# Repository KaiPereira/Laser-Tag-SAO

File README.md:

# Laser Tag SAOs

These are little badge add-ons so you can play laser-tag against your friends :D 

- VSLY5940 Narrow beam IR transmitter
- TSOP38438 IR receiver
- NPN for turning on the IR transmitter
- SMD4020 side mount neopixels
- 0.91" 128x32 OLED/display for funsies
- PS1240P02BT Piezo buzzer
- Button to shoot and a button to change modes or other stuff
- 1 SAO port
- ATtiny84 DIP 14

## Firmware

You can program the laser tag guns over SPI broken out over the SAO connector.

First bridge the jumpers on the back with solder.

Next, you'll need to setup your Arduino as an ISP. I've set mine up for use with the Pi Pico, so you'll need to modify the ISP code for other boards. 
- Select your board by going tools -> boards -> whatever board you're using. For the raspberry pi, you'll need to install it in the board manager tab. 
- Upload the ArduinoISP code in [/programming/ArduinoISP](/programming/ArduinoISP).

Then you should open up the PCB in KiCad and wire up the SAO connector to the Pi Pico, I'll make a second version with silkscreen labels in the future:
- 3.3V to 3.3V
- GND to GND
- IO19 to MOSI
- IO18 to SCK
- IO16 to MISO
- GPIO10 to RESET

Then change the board to be the ATtiny24/44/84 No bootloader from the ATTinyCore library and set tools -> programmer to be "Arduino as ISP".

Next run tools -> burn bootloader and then upload the ATtiny code in [/programming/laser-tag](/programming/laser-tag) and you're all flashed!

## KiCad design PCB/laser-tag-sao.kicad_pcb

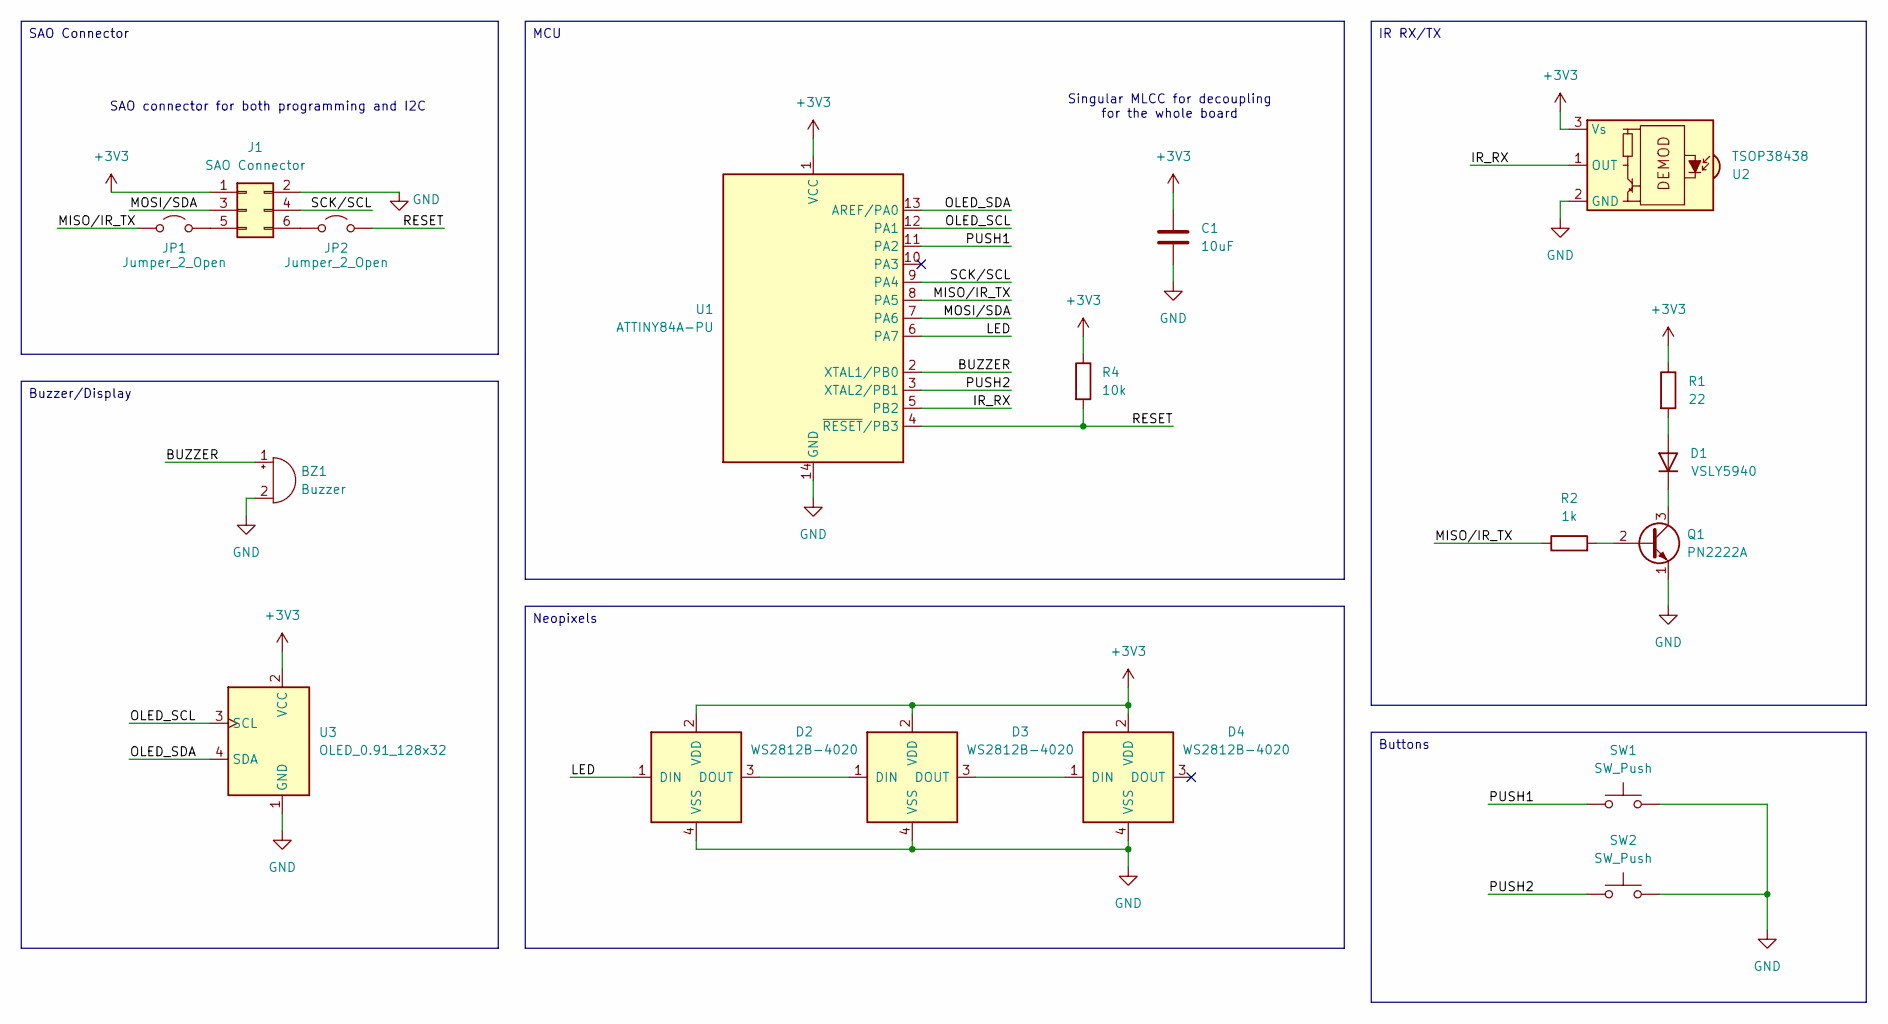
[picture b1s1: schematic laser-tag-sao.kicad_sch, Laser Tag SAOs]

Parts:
BZ1: Buzzer; Buzzer_TDK_PS1240P02BT_D12.2mm_H6.5mm; Digikey Part # 445-2525-1-ND - Cut Tape (CT)
C1: 10uF; C_Disc_D5.0mm_W2.5mm_P2.50mm; Digikey Part # 445-173132-1-ND - Cut Tape (CT)
D1: VSLY5940; LED_D5.0mm; Digikey Part # VSLY5940-ND
D2, D3, D4: WS2812B-4020; LED_WS2812B-4020; PARTREV V1.2
J1: SAO Connector; PinHeader_2x03_P2.54mm_Vertical
JP1, JP2: Jumper_2_Open; SolderJumper-2_P1.3mm_Open_RoundedPad1.0x1.5mm
Q1: PN2222A; TO-92_Inline
R1: 22; R_Axial_DIN0204_L3.6mm_D1.6mm_P5.08mm_Horizontal; Digikey Part # CF18JT22R0TR-ND - Tape & Reel (TR)
R2: 1k; R_Axial_DIN0204_L3.6mm_D1.6mm_P5.08mm_Horizontal; Digikey Part # CF18JT1K00TR-ND - Tape & Reel (TR)
R4: 10k; R_Axial_DIN0204_L3.6mm_D1.6mm_P5.08mm_Horizontal; Digikey Part # CF18JT10K0TR-ND - Tape & Reel (TR)
SW1: SW_Push; SW_PUSH_6mm; Digikey Part # 450-1650-ND
SW2: SW_Push; SW_PUSH_6mm
U1: ATTINY84A-PU; DIP-14_W7.62mm; Digikey Part # ATTINY84A-PU-ND
U2: TSOP38438; Vishay_MINICAST-3Pin; Digikey Part # TSOP38438-ND
U3: OLED_0.91_128x32

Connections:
+3V3: C1.1, D2.2 (VDD), D3.2 (VDD), D4.2 (VDD), J1.1, R1.1, R4.1, U1.1 (VCC), U2.3 (Vs), U3.2 (VCC)
/BUZZER: BZ1.1 (+), U1.2 (XTAL1/PB0)
/IR_RX: U1.5 (PB2), U2.1 (OUT)
/LED: D2.1 (DIN), U1.6 (PA7)
/MISO/IR_TX: JP1.1 (A), R2.1, U1.8 (PA5)
/MOSI/SDA: J1.3, U1.7 (PA6)
/OLED_SCL: U1.12 (PA1), U3.3 (SCL)
/OLED_SDA: U1.13 (AREF/PA0), U3.4 (SDA)
/PUSH1: SW1.1, U1.11 (PA2)
/PUSH2: SW2.1, U1.3 (XTAL2/PB1)
/RESET: JP2.2 (B), R4.2, U1.4 (~RESET/PB3)
/SCK/SCL: J1.4, U1.9 (PA4)
GND: BZ1.2 (-), C1.2, D2.4 (VSS), D3.4 (VSS), D4.4 (VSS), J1.2, Q1.1 (E), SW1.2, SW2.2, U1.14 (GND), U2.2 (GND), U3.1 (GND)
unnamed: D1.2 (A), R1.2
unnamed: D1.1 (K), Q1.3 (C)
unnamed: D2.3 (DOUT), D3.1 (DIN)
unnamed: D3.3 (DOUT), D4.1 (DIN)
unnamed: J1.5, JP1.2 (B)
unnamed: J1.6, JP2.1 (A)
unnamed: Q1.2 (B), R2.2

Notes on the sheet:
SAO connector for both programming and I2C
Singular MLCC for decoupling for the whole board
IR RX/TX
Neopixels
Buzzer/Display
Buttons
SAO Connector
MCU

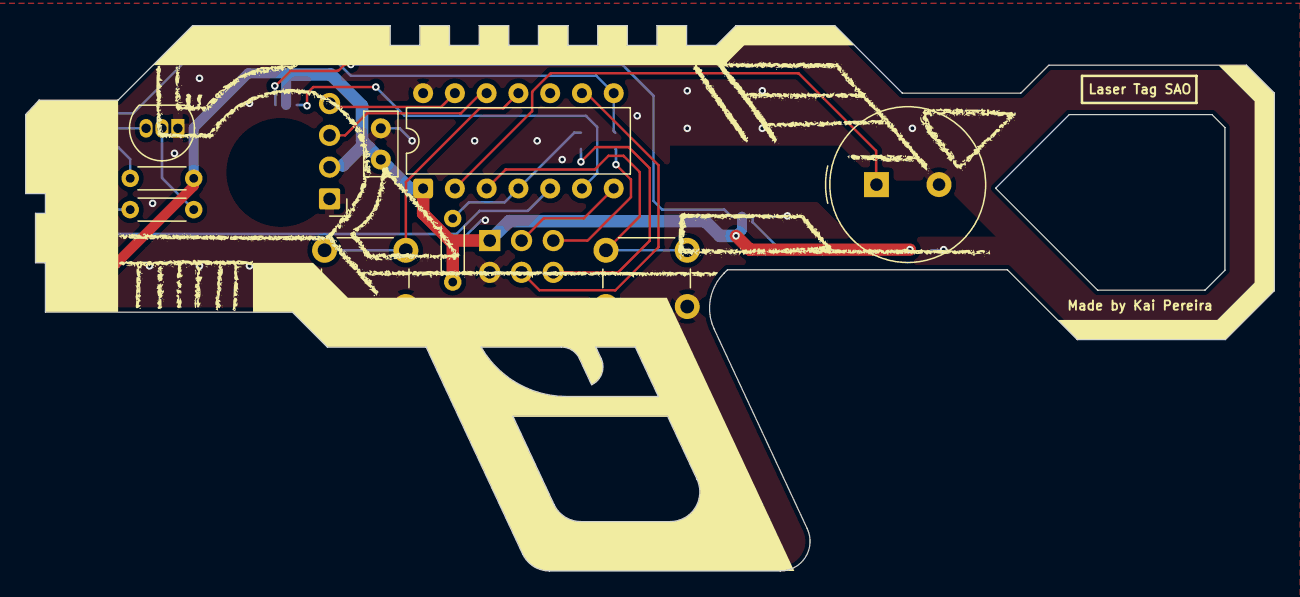
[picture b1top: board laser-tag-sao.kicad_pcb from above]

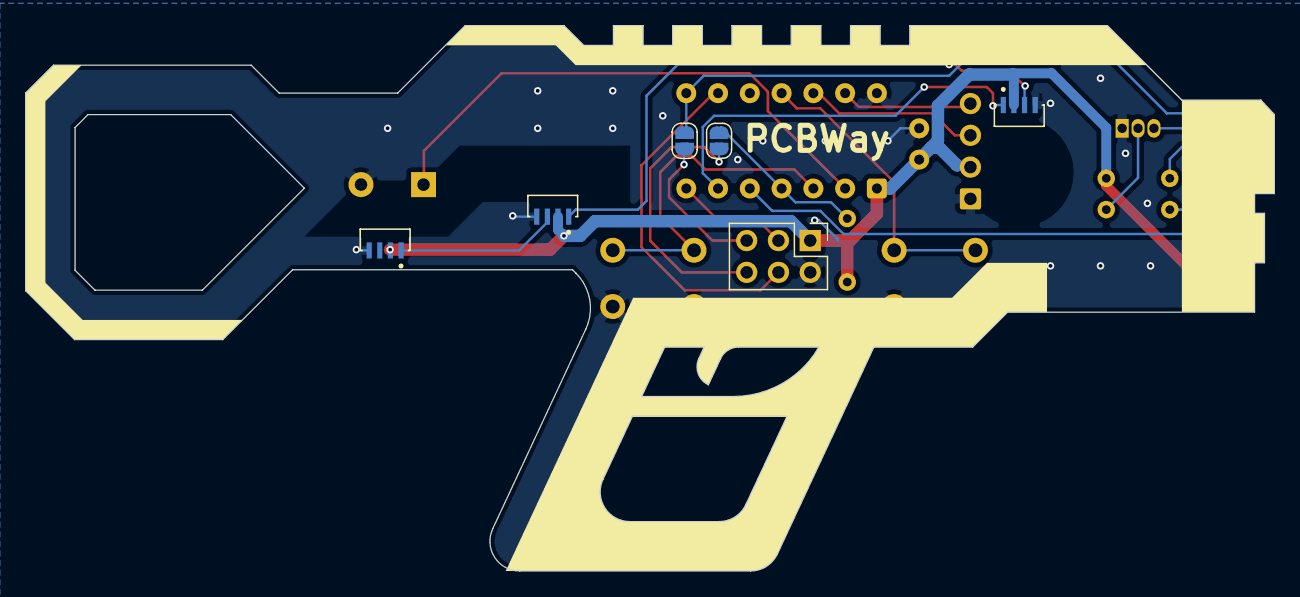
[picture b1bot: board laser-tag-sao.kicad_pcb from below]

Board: 2 copper layers, 99.8 x 43.6 mm, 18 parts (6 on the bottom side), 20 nets.

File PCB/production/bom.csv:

Designator,Footprint,Quantity,Value,LCSC Part #
BZ1,Buzzer_TDK_PS1240P02BT_D12.2mm_H6.5mm,1,Buzzer,
C1,C_Disc_D5.0mm_W2.5mm_P2.50mm,1,10uF,
D1,LED_D5.0mm,1,VSLY5940,
"D2, D3, D4",LED_WS2812B-4020,3,WS2812B-4020,
J1,PinHeader_2x03_P2.54mm_Vertical,1,SAO Connector,
"JP1, JP2",SolderJumper-2_P1.3mm_Open_RoundedPad1.0x1.5mm,2,Jumper_2_Open,
Q1,TO-92_Inline,1,PN2222A,
R1,R_Axial_DIN0204_L3.6mm_D1.6mm_P5.08mm_Horizontal,1,22,
R2,R_Axial_DIN0204_L3.6mm_D1.6mm_P5.08mm_Horizontal,1,1k,
R4,R_Axial_DIN0204_L3.6mm_D1.6mm_P5.08mm_Horizontal,1,10k,
"SW1, SW2",SW_PUSH_6mm,2,SW_Push,
U1,DIP-14_W7.62mm,1,ATTINY84A-PU,
U2,Vishay_MINICAST-3Pin,1,TSOP38438,
U3,OLED_0.91_128x32,1,OLED_0.91_128x32,

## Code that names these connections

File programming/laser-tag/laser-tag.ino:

// Laser tag blaster for ATtiny84 (ATTinyCore)
//
//   Button    PA2 (physical pin 11) -> GND, uses internal pull-up
//   IR TX     PA5 (physical pin 8)  -> NPN base resistor -> VSLY5940
//   Buzzer    PB0 (physical pin 2)
//   IR RX     PB2 (physical pin 5)  <- 38 kHz IR receiver output (TSOP-style, active LOW)
//
// Set Tools > Clock to "8 MHz (internal)" before uploading. setup() also
// clears the clock divider, so Burn Bootloader isn't strictly needed.
//
// IR safety: each shot is ~10 ms of short bursts at <=50% carrier duty,
// with a forced cooldown between shots and the pin always left LOW.

#include <util/delay.h>
#include <avr/power.h>

#ifdef PIN_PA2
  #define BUTTON   PIN_PA2
  #define BUZZER   PIN_PB0
  #define IR_RX    PIN_PB2
#else
  #define BUTTON   2    // ATTinyCore default (counterclockwise) pinmap
  #define BUZZER   10
  #define IR_RX    8
#endif

#define IR_BIT (1 << 5)  // PA5, driven directly on PORTA for accurate timing

// Receiver debug: set to 1 and the buzzer beeps for as long as the IR receiver
// sees any 38 kHz IR (a TV remote, another badge, or this badge's own shot
// bouncing back). Normal hit detection is skipped. Set to 0 for real games.
#define DEBUG_RX 0

// The TSOP38438 receiver is a short-burst (AGC4) type: it treats one long
// continuous 38 kHz burst as noise and suppresses it. So a shot is a train of
// short bursts, like a TV remote, and a hit means seeing enough of them in a row.
const uint8_t  SHOT_PULSES     = 8;     // bursts per shot
const uint8_t  PULSE_CYCLES    = 24;    // ~630 us of 38 kHz per burst
#define        PULSE_GAP_US      630    // IR off between bursts

// Shot power: microseconds the LED is ON in each ~26 us carrier cycle.
// 13 = 50% duty (full power, bounces off walls and hits from anywhere).
// Lower = weaker shot, so only a direct hit counts. The receiver still sees
// the 38 kHz carrier down to ~2. Tune this to taste: try 4, then 2-6.
#define        IR_ON_US          4
const uint8_t  HIT_MIN_PULSES  = 4;     // bursts that must be seen to count as a hit
const uint16_t PULSE_MIN_US    = 200;   // receiver LOW pulse width accepted as a burst
const uint16_t PULSE_MAX_US    = 1500;
const uint16_t GAP_MAX_US      = 1500;  // longer silence ends the shot
const uint16_t COOLDOWN_MS     = 300;   // minimum time between shots (no auto-fire)
const uint16_t HIT_LOCKOUT_MS  = 1000;  // one bolt = one hit
const uint16_t SELF_IGNORE_MS  = 50;    // ignore our own shot's reflections

unsigned long lastShot = 0;
unsigned long lastHit = 0;
bool wasPressed = false;

void irOff() {
  PORTA &= ~IR_BIT;
}

// One shot: SHOT_PULSES short 38 kHz bursts with gaps between them.
// Interrupts are paused so the carrier stays clean.
void fireShot() {
  noInterrupts();
  for (uint8_t p = 0; p < SHOT_PULSES; p++) {
    for (uint8_t i = 0; i < PULSE_CYCLES; i++) {
      PORTA |= IR_BIT;
      _delay_us(IR_ON_US);
      PORTA &= ~IR_BIT;
      _delay_us(25 - IR_ON_US);  // ~1 us of loop overhead at 8 MHz
    }
    _delay_us(PULSE_GAP_US);
  }
  irOff();
  interrupts();
}

// Descending "pew" laser sound, about 130 ms.
void pew() {
  for (int f = 3000; f > 400; f -= 100) {
    tone(BUZZER, f);
    delay(5);
  }
  noTone(BUZZER);
  digitalWrite(BUZZER, LOW);
}

// "You got hit": a crunchy falling zap, then a two-note "you're down" sting.
// About 0.8 s total.
void hitSound() {
  // Falling zap; alternating between f and 3/4 f gives it a gritty, electric edge
  for (int f = 1800; f > 150; f -= 40) {
    tone(BUZZER, ((f / 40) % 2) ? f : f * 3 / 4);
    delay(8);
  }
  noTone(BUZZER);
  delay(60);

  // Two descending notes
  tone(BUZZER, 400);
  delay(120);
  noTone(BUZZER);
  delay(40);
  tone(BUZZER, 250);
  delay(250);

  noTone(BUZZER);
  digitalWrite(BUZZER, LOW);
}

// Returns true if the receiver shows a shot: several short LOW pulses in a row.
// The first pulse can be any length, since we may have started watching midway.
bool checkForBolt() {
  if (digitalRead(IR_RX) == HIGH) return false;  // nothing seen

  uint8_t pulses = 0;
  while (true) {
    // Receiver LOW = burst
    unsigned long start = micros();
    while (digitalRead(IR_RX) == LOW) {
      if (micros() - start > PULSE_MAX_US) {
        // Too long to be one of our bursts: let it clear (bounded) and give up
        unsigned long t = micros();
        while (digitalRead(IR_RX) == LOW && micros() - t < 50000UL) {}
        return false;
      }
    }
    if (pulses > 0 && micros() - start < PULSE_MIN_US) return false;  // glitch
    if (++pulses >= HIT_MIN_PULSES) return true;

    // Receiver HIGH = gap; wait for the next burst
    start = micros();
    while (digitalRead(IR_RX) == HIGH) {
      if (micros() - start > GAP_MAX_US) return false;
    }
  }
}

void setup() {
  // New ATtiny84s ship with the CKDIV8 fuse set (8 MHz / 8 = 1 MHz), which makes
  // every sound 8x slower and deeper and puts the IR carrier at ~5 kHz.
  // Force the full 8 MHz in software so it works even if the fuses were never burned.
  clock_prescale_set(clock_div_1);

  irOff();          // LOW before making it an output, so the LED never blips on
  DDRA |= IR_BIT;
  pinMode(BUZZER, OUTPUT);
  pinMode(BUTTON, INPUT_PULLUP);
  pinMode(IR_RX, INPUT_PULLUP);  // most receivers have one built in; this doesn't hurt
}

void loop() {
#if DEBUG_RX
  static bool beeping = false;
  static unsigned long lastSeen = 0;
  if (digitalRead(IR_RX) == LOW) lastSeen = millis();
  bool seeing = (millis() - lastSeen < 100);  // stretch short shots so you can hear them
  if (seeing && !beeping) tone(BUZZER, 2000);
  if (!seeing && beeping) { noTone(BUZZER); digitalWrite(BUZZER, LOW); }
  beeping = seeing;
  // One shot per press (no pew, so you only hear the receiver)
  bool dbgPressed = (digitalRead(BUTTON) == LOW);
  if (dbgPressed && !wasPressed && millis() - lastShot >= COOLDOWN_MS) {
    lastShot = millis();
    fireShot();
  }
  wasPressed = dbgPressed;
  return;
#endif

  unsigned long now = millis();
  bool pressed = (digitalRead(BUTTON) == LOW);

  // Fire once per press, and only after the cooldown
  if (pressed && !wasPressed && (now - lastShot >= COOLDOWN_MS)) {
    lastShot = now;
    fireShot();  // IR first, so the buzzer's timer doesn't disturb it
    pew();
  }
  wasPressed = pressed;

  // Hit detection, skipping right after our own shot and during the hit lockout
  if ((millis() - lastShot >= SELF_IGNORE_MS) &&
      (millis() - lastHit >= HIT_LOCKOUT_MS) &&
      checkForBolt()) {
    lastHit = millis();
    hitSound();
  }

  irOff();   // belt and braces: IR is always off between shots
  delay(1);  // short loop so a 10 ms bolt is never missed
}
